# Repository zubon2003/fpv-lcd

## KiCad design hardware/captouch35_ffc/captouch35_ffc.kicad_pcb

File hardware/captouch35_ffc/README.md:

# バンドモニター本体基板 (FFC 版) + 電池サブ基板

Waveshare 3.5inch Capacitive Touch LCD の裏に M2.5 の六角スペーサー (長さ 15mm、オス-メス) で重ねる XIAO ESP32-C5 の基板。
液晶とは 18 ピンの FFC (0.5mm) でつなぐ。電池のサブ基板 (BT2.0 だけ) を右にミシン目でつないだ 1 枚のパネル。
ピンは fpv_config.h の FPV_PANEL_CAPTOUCH35 と同じなので、ファームは今のまま使える。

- `captouch35_ffc.kicad_pcb`: KiCad 8 の基板 (回路図はない。結線は下のとおり)。フットプリントは `captouch35_ffc.pretty`
- `drc.rpt`: DRC の結果 (違反 0、未接続 0)
- `jlcpcb/`: ガーバー zip、BOM、CPL (部品の位置)
- `preview_top.pdf` (外側から見た図)、`preview_bottom.pdf` (液晶側)、`preview.svg`

## 形
- 本体: 83.44 x 55.16mm (液晶の基板と同じ)。M2.5 の穴が四隅 (端から 4.8mm)、液晶の穴と同じ位置
- 図は外側 (液晶と反対の面) から見たもの。液晶を裏から見た向きと同じ
- XIAO: 外側の面、USB-C は下の辺 (1.3mm はみ出す)、U.FL は上を向く → SMA / RP-SMA のピグテールで上へ (付属のアンテナなら U.FL に直接)
- FFC: 液晶のコネクタ (裏の右端) のすぐ左にスロット (1.6 x 12mm) があり、ケーブルはそこから外側へ抜けて左へ進み、J1 に入る
- ロゴ (シルク): ZUBON TECH. (上) と Tinywhoop (右下)。基板ファイルに入っている
- サブ基板: 12 x 16mm、M2 の穴 2 つ。本体の右の辺とタブ (幅 5mm、Ø0.5 の穴 5 つ x 2 列) でつながっている。手で折って外す

## 結線
| FFC ピン | 液晶 | XIAO | 層 |
|---|---|---|---|
| 1 | VCC | 3V3 | 表 |
| 2 | LCD_BL | D5 | 裏 |
| 3 | GND | GND | ベタ |
| 4 | SCLK | D9 | 表 |
| 5 | MOSI | D10 | 表 |
| 7 | LCD_DC | D7 | 裏 |
| 8 | LCD_RST | D6 | 裏 |
| 9 | LCD_CS | D8 | 裏 |
| 12 | TP_RST | D0 | 表 |
| 13 | TP_SCL | D1 | 表 |
| 14 | TP_SDA | D4 | 表 |
| 6, 10, 11, 15-18 | MISO, SD_CS, NC, TP_INT, NC | つながない | |

電池: BT2.0 (サブ基板の J4) の足から電線で、+ は XIAO の BAT+、- は XIAO の BAT- へ (XIAO の裏のパッド)。

## 部品
| 記号 | 部品 | 付け方 |
|---|---|---|
| J1 | FFC コネクタ 18P 0.5mm、上下両面接点、フリップロック (HDGC 0.5K-HX-18PWB、LCSC C2919497、拡張部品) | JLCPCB が実装 |
| J2, J3 | XIAO 用のピンソケット: 分割ロングピンソケット 1x42 (秋月 105779、FHU-1x42SG) を 7 ピンずつに切る。XIAO には付属のピンヘッダーを付けて挿す。ソケットを使わず、ピンヘッダーを直接はんだ付けしてもよい | 自分で |
| J4 | BT2.0 メス (BETAFPV) | 自分で |
| | M2 六角スペーサー 6mm x 2、M2 ねじ (BT2.0 のサブ基板の固定) | |
| | FFC ケーブル 18P 0.5mm、長さ 50mm (長くてもとりあえず大丈夫。接点タイプは A / B どちらでもよい) | |
| | M2.5 六角スペーサー 長さ 15mm、片側オスねじ・片側メスねじ x 4 (オス側は液晶のメスねじへ、メス側はケースを留めるねじ用) | |
| | M2.5 プラスチックねじ x 4 (ケースをスペーサーのメス側に留める) | |
| | U.FL - SMA / RP-SMA (パネル取り付け) のピグテール (手持ちのアンテナに合わせる。XIAO ESP32-C5 付属のアンテナを使う場合は不要) | |

## 組み立ての注意
- **XIAO を付ける前に**、XIAO の裏の BAT+ / BAT- のパッドに電線を付け、上 (アンテナ側) へ出しておく (付けた後は基板とのすき間に隠れる)
- 液晶側に出たピンソケットの足は短く切る (液晶の裏の部品に当たらないように。設計時の想定はすき間 8mm)
- FFC は両面接点なので、ケーブルの接点の向き (A/B) は気にしなくてよい。ピン 1 は液晶側もこちらも上の端
- 長さ 50mm は計算上の値 (液晶のコネクタ → スロット → J1)。余ったらスロットの外側で軽くたわませる

## 注文前に確かめること
- `preview_top.pdf` を原寸で印刷し、液晶の裏に重ねて、四隅の穴と FFC コネクタの位置 (スロットのすぐ右に来るか) を確かめる。
  液晶のコネクタの位置は、Waveshare の 3D データから読んだ値

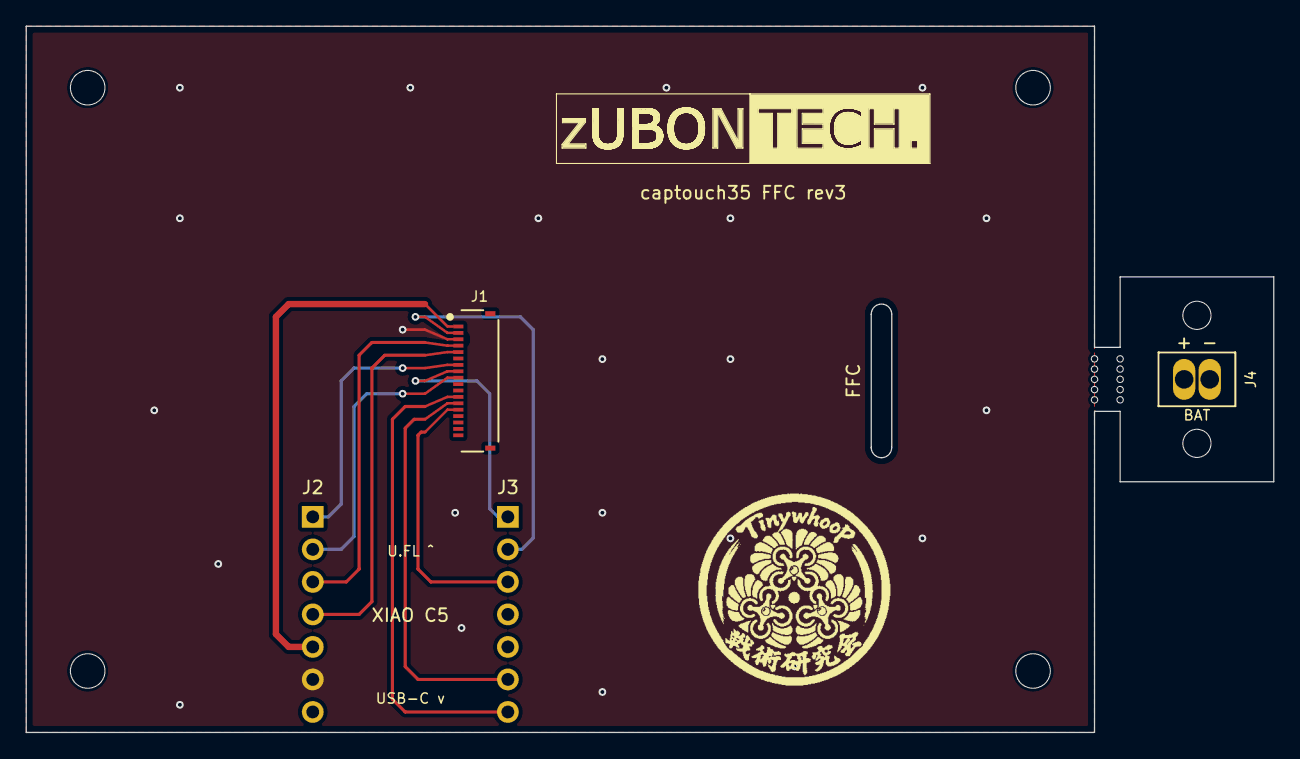
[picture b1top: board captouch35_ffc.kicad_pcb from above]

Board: 2 copper layers, 97.4 x 55.2 mm, 14 parts (0 on the bottom side), 11 nets.

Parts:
G1: LOGO_ZUBONTECH_RX5808v3_x2
G2: LOGO; LOGO_TinywhoopLab_15mm
H1, H2, H3, H4: MountingHole_2.7mm_M2.5
H5, H6: MountingHole_2.2mm_M2
J1: 0.5K-HX-18PWB; FFC_18P_P0.5_HDGC_0.5K-HX-18PWB
J2, J3: XIAO; PinHeader_1x07_P2.54mm_Vertical
J4: BT2.0; BETAFPV_BT2.0_Vertical
MB1, MB2: MouseBite; MouseBite_5x0.5mm

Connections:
3V3: J1.1, J2.5
GND: J1.3, J2.6
LCD_BL: J1.2, J3.2
LCD_CS: J1.9, J2.2
LCD_DC: J1.7, J2.1
LCD_RST: J1.8, J3.1
MOSI: J1.5, J2.4
SCLK: J1.4, J2.3
TP_RST: J1.12, J3.7
TP_SCL: J1.13, J3.6
TP_SDA: J1.14, J3.3
